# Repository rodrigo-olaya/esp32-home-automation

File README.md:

# esp32-home-automation
Project to make my home smart using several ESP32 MCUs, and sensors.

## Layout
- [temperature-control](temperature-control): temperature and humidity monitoring (the old thermostat motor code is in `temperature-control/legacy/motor`)
- [bringup](bringup): small programs to check the DevKit and the carrier board, flashed with `make flash-<name>`
- [security-camera](security-camera): camera node publishing frames over MQTT
- [hardware/esp32_carrier_board](hardware/esp32_carrier_board): carrier PCB for the DevKit

All nodes talk MQTT to the broker on the Raspberry Pi and are built with ESP-IDF.

## Main Components
This Smart Home system has the following features:
- Temperature Monitoring
- Humidity Monitoring
- Security Camera

### Temperature Monitoring
Temperature is monitored using a DS18B20 sensor, which uses the 1-Wire protocol to communicate with an ESP32.

### Humidity Monitoring
Humidity is monitored using an SHT31 sensor, which uses I2C to communicate with ESP32

## Hardware
The ESP32 home node carrier board (KiCad project, Gerbers, BOM, renders) is in [hardware/esp32_carrier_board](hardware/esp32_carrier_board).

Top and bottom views: [render_top.png](hardware/esp32_carrier_board/fab/render_top.png), [render_bottom.png](hardware/esp32_carrier_board/fab/render_bottom.png).

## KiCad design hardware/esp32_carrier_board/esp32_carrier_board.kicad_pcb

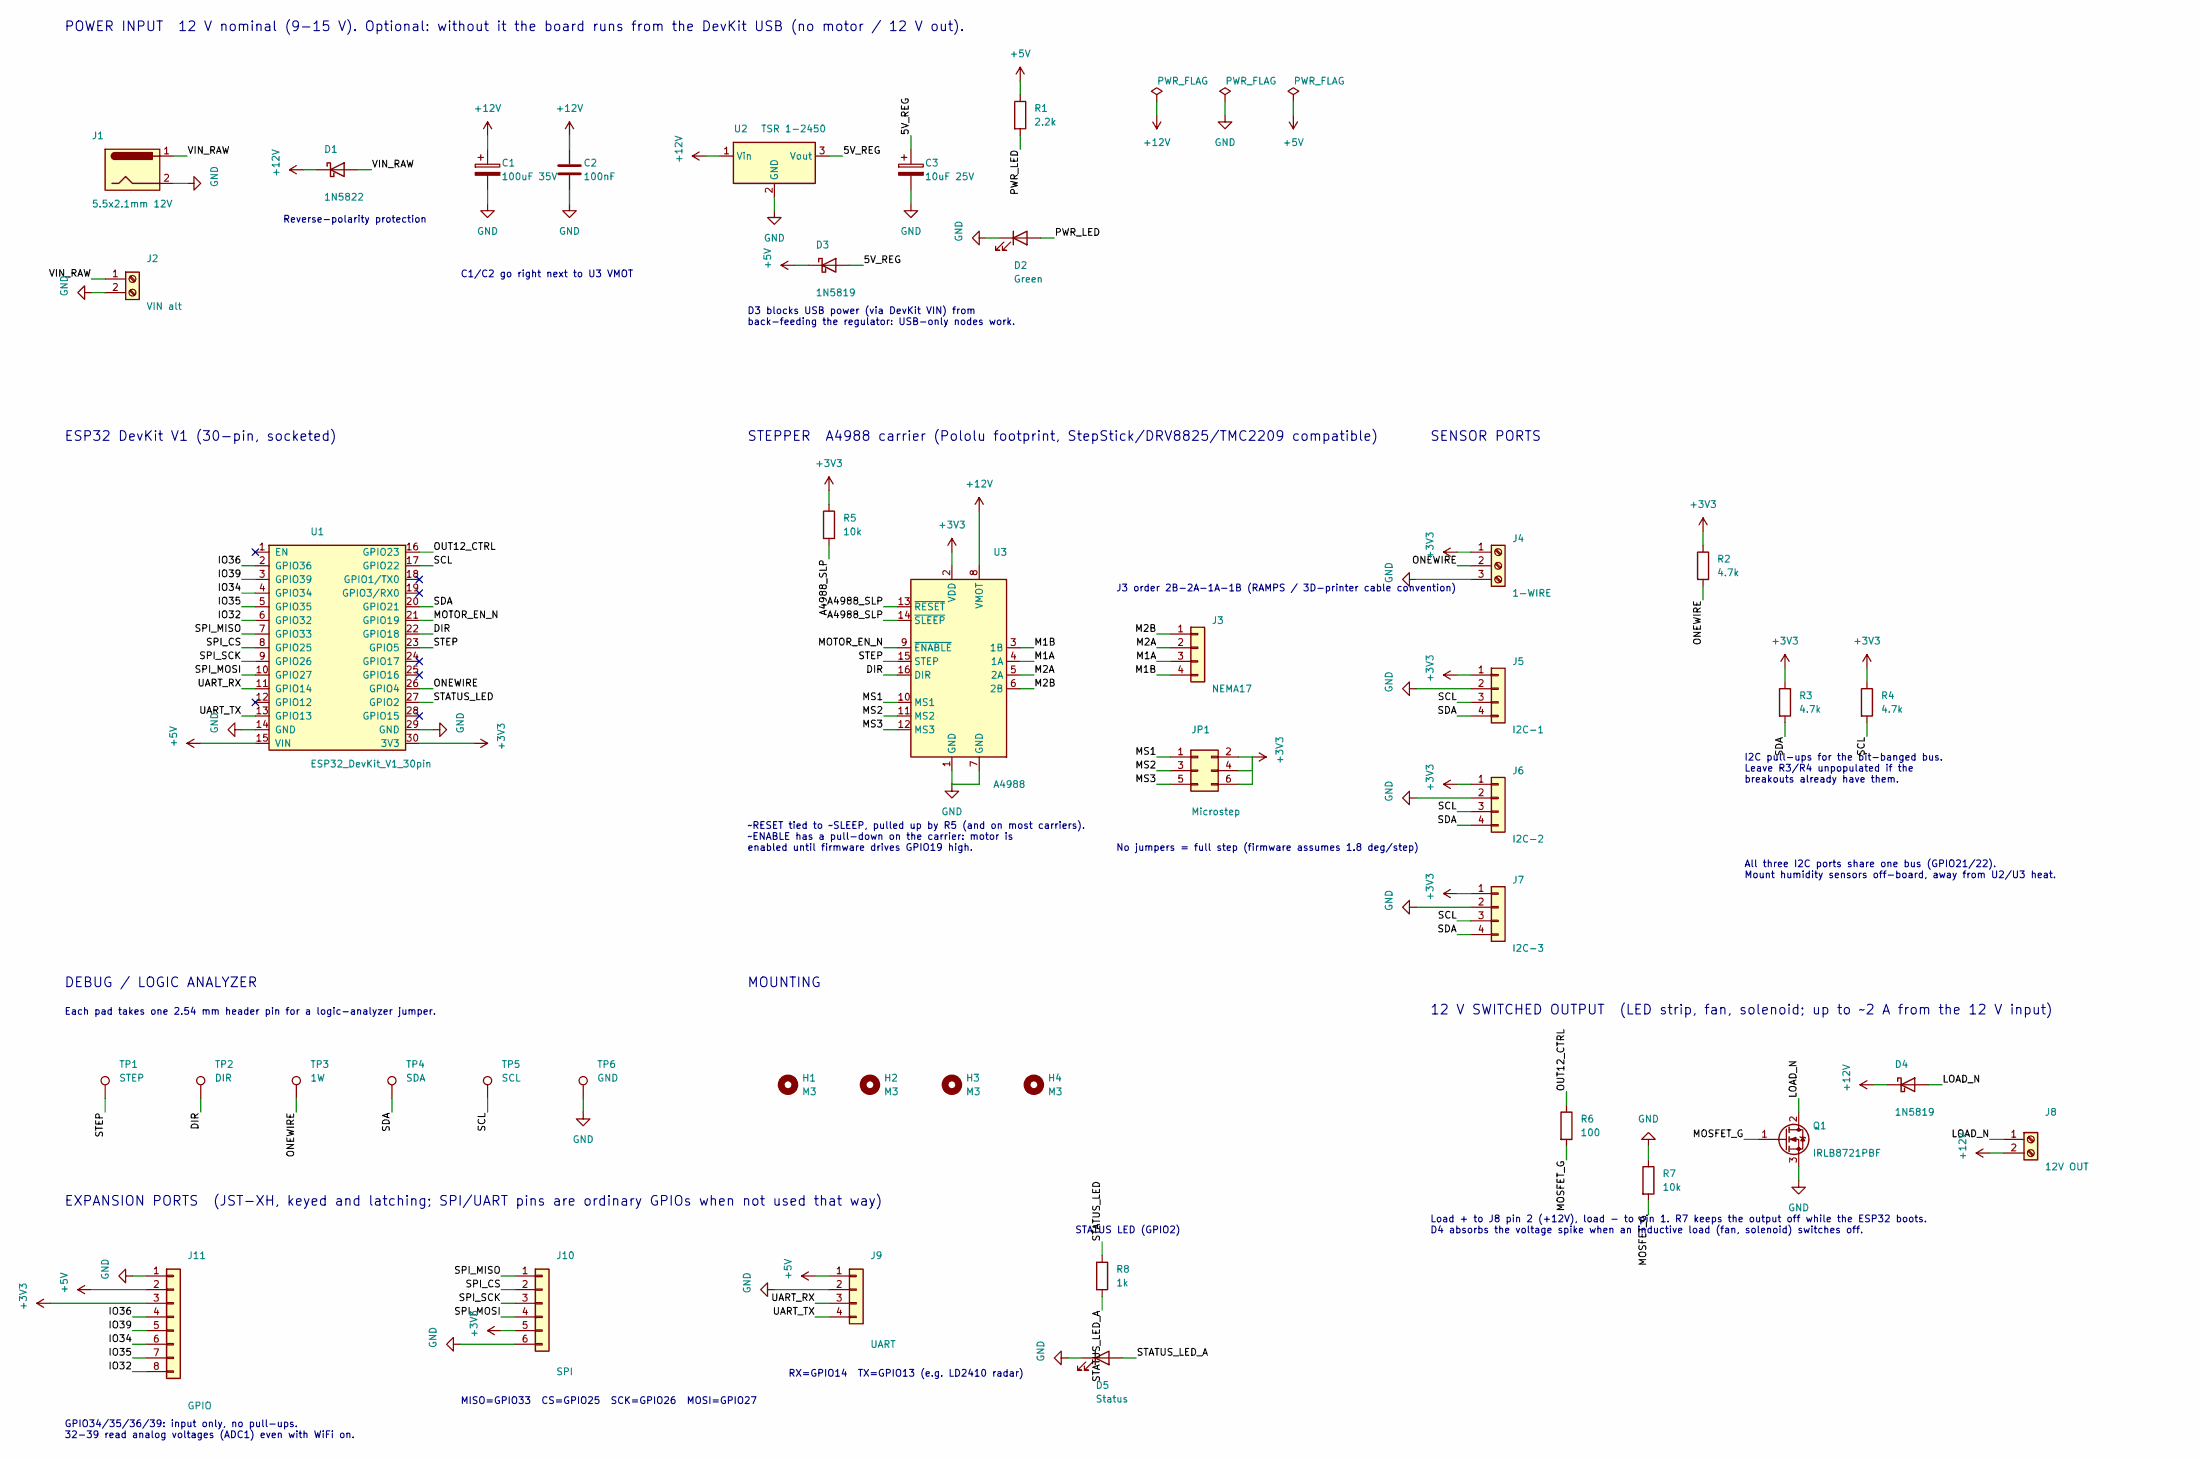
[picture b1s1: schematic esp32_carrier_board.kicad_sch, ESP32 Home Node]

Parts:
C1: 100uF 35V; CP_Radial_D8.0mm_P3.50mm
C2: 100nF; C_Disc_D5.0mm_W2.5mm_P5.00mm
C3: 10uF 25V; CP_Radial_D5.0mm_P2.00mm
D1: 1N5822; D_DO-201AD_P15.24mm_Horizontal
D2: Green; LED_D5.0mm
D3, D4: 1N5819; D_DO-41_SOD81_P2.54mm_Vertical_AnodeUp
D5: Status; LED_D5.0mm
H1, H2, H3, H4: M3; MountingHole_3.2mm_M3
J1: 5.5x2.1mm 12V; BarrelJack_Horizontal
J2: VIN alt; TerminalBlock_Phoenix_MKDS-1,5-2-5.08_1x02_P5.08mm_Horizont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
J3: NEMA17; JST_XH_B4B-XH-A_1x04_P2.50mm_Vertical
J4: 1-WIRE; TerminalBlock_Phoenix_MKDS-1,5-3-5.08_1x03_P5.08mm_Horizont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
J5: I2C-1; JST_XH_B4B-XH-A_1x04_P2.50mm_Vertical
J6: I2C-2; JST_XH_B4B-XH-A_1x04_P2.50mm_Vertical
J7: I2C-3; JST_XH_B4B-XH-A_1x04_P2.50mm_Vertical
J8: 12V OUT; TerminalBlock_Phoenix_MKDS-1,5-2-5.08_1x02_P5.08mm_Horizont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
J9: UART; JST_XH_B4B-XH-A_1x04_P2.50mm_Vertical
J10: SPI; JST_XH_B6B-XH-A_1x06_P2.50mm_Vertical
J11: GPIO; JST_XH_B8B-XH-A_1x08_P2.50mm_Vertical
JP1: Microstep; PinHeader_2x03_P2.54mm_Vertical
Q1: IRLB8721PBF; TO-220-3_Vertical
R1: 2.2k; R_Axial_DIN0207_L6.3mm_D2.5mm_P10.16mm_Horizontal
R2, R3, R4: 4.7k; R_Axial_DIN0207_L6.3mm_D2.5mm_P10.16mm_Horizontal
R5: 10k; R_Axial_DIN0207_L6.3mm_D2.5mm_P10.16mm_Horizontal
R6: 100; R_Axial_DIN0207_L6.3mm_D2.5mm_P2.54mm_Vertical
R7: 10k; R_Axial_DIN0207_L6.3mm_D2.5mm_P2.54mm_Vertical
R8: 1k; R_Axial_DIN0207_L6.3mm_D2.5mm_P7.62mm_Horizontal
TP1: STEP; TestPoint_THTPad_D2.0mm_Drill1.0mm
TP2: DIR; TestPoint_THTPad_D2.0mm_Drill1.0mm
TP3: 1W; TestPoint_THTPad_D2.0mm_Drill1.0mm
TP4: SDA; TestPoint_THTPad_D2.0mm_Drill1.0mm
TP5: SCL; TestPoint_THTPad_D2.0mm_Drill1.0mm
TP6: GND; TestPoint_THTPad_D2.0mm_Drill1.0mm
U1: ESP32_DevKit_V1_30pin; ESP32_DevKit_V1_30pin_Socket
U2: TSR 1-2450; Converter_DCDC_TRACO_TSR-1_THT
U3: A4988; Pololu_Breakout-16_15.2x20.3mm

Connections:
+3V3: J4.1, J5.1, J6.1, J7.1, J10.5, J11.3, JP1.2, JP1.4, JP1.6, R2.1, R3.1, R4.1, R5.1, U1.30 (3V3), U3.2 (VDD)
+5V: D3.1 (K), J9.1, J11.2, R1.1, U1.15 (VIN)
+12V: C1.1, C2.1, D1.1 (K), D4.1 (K), J8.2, U2.1 (Vin), U3.8 (VMOT)
/5V_REG: C3.1, D3.2 (A), U2.3 (Vout)
/A4988_SLP: R5.2, U3.13 (~RESET), U3.14 (~SLEEP)
/DIR: TP2.1, U1.22 (GPIO18), U3.16 (DIR)
/IO32: J11.8, U1.6 (GPIO32)
/IO34: J11.6, U1.4 (GPIO34)
/IO35: J11.7, U1.5 (GPIO35)
/IO36: J11.4, U1.2 (GPIO36)
/IO39: J11.5, U1.3 (GPIO39)
/LOAD_N: D4.2 (A), J8.1, Q1.2 (D)
/M1A: J3.3, U3.4 (1A)
/M1B: J3.4, U3.3 (1B)
/M2A: J3.2, U3.5 (2A)
/M2B: J3.1, U3.6 (2B)
/MOSFET_G: Q1.1 (G), R6.2, R7.2
/MOTOR_EN_N: U1.21 (GPIO19), U3.9 (~ENABLE)
/MS1: JP1.1, U3.10 (MS1)
/MS2: JP1.3, U3.11 (MS2)
/MS3: JP1.5, U3.12 (MS3)
/ONEWIRE: J4.2, R2.2, TP3.1, U1.26 (GPIO4)
/OUT12_CTRL: R6.1, U1.16 (GPIO23)
/PWR_LED: D2.2 (A), R1.2
/SCL: J5.3, J6.3, J7.3, R4.2, TP5.1, U1.17 (GPIO22)
/SDA: J5.4, J6.4, J7.4, R3.2, TP4.1, U1.20 (GPIO21)
/SPI_CS: J10.2, U1.8 (GPIO25)
/SPI_MISO: J10.1, U1.7 (GPIO33)
/SPI_MOSI: J10.4, U1.10 (GPIO27)
/SPI_SCK: J10.3, U1.9 (GPIO26)
/STATUS_LED: R8.1, U1.27 (GPIO2)
/STATUS_LED_A: D5.2 (A), R8.2
/STEP: TP1.1, U1.23 (GPIO5), U3.15 (STEP)
/UART_RX: J9.3, U1.11 (GPIO14)
/UART_TX: J9.4, U1.13 (GPIO13)
/VIN_RAW: D1.2 (A), J1.1, J2.1
GND: C1.2, C2.2, C3.2, D2.1 (K), D5.1 (K), J1.2, J2.2, J4.3, J5.2, J6.2, J7.2, J9.2, J10.6, J11.1, Q1.3 (S), R7.1, TP6.1, U1.14 (GND), U1.29 (GND), U2.2 (GND), U3.1 (GND), U3.7 (GND)

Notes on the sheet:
POWER INPUT 12 V nominal (9-15 V). Optional: without it the board runs from the DevKit USB (no motor / 12 V out).
Reverse-polarity protection
C1/C2 go right next to U3 VMOT
D3 blocks USB power (via DevKit VIN) from back-feeding the regulator: USB-only nodes work.
ESP32 DevKit V1 (30-pin, socketed)
STEPPER A4988 carrier (Pololu footprint, StepStick/DRV8825/TMC2209 compatible)
~RESET tied to ~SLEEP, pulled up by R5 (and on most carriers). ~ENABLE has a pull-down on the carrier: motor is enabled until firmware drives GPIO19 high.
No jumpers = full step (firmware assumes 1.8 deg/step)
J3 order 2B-2A-1A-1B (RAMPS / 3D-printer cable convention)
SENSOR PORTS
I2C pull-ups for the bit-banged bus. Leave R3/R4 unpopulated if the breakouts already have them.
All three I2C ports share one bus (GPIO21/22). Mount humidity sensors off-board, away from U2/U3 heat.
DEBUG / LOGIC ANALYZER
Each pad takes one 2.54 mm header pin for a logic-analyzer jumper.
MOUNTING
12 V SWITCHED OUTPUT (LED strip, fan, solenoid; up to ~2 A from the 12 V input)
Load + to J8 pin 2 (+12V), load - to pin 1. R7 keeps the output off while the ESP32 boots. D4 absorbs the voltage spike when an inductive load (fan, solenoid) switches off.
EXPANSION PORTS (JST-XH, keyed and latching; SPI/UART pins are ordinary GPIOs when not used that way)
GPIO34/35/36/39: input only, no pull-ups. 32-39 read analog voltages (ADC1) even with WiFi on.
MISO=GPIO33 CS=GPIO25 SCK=GPIO26 MOSI=GPIO27
RX=GPIO14 TX=GPIO13 (e.g. LD2410 radar)
STATUS LED (GPIO2)

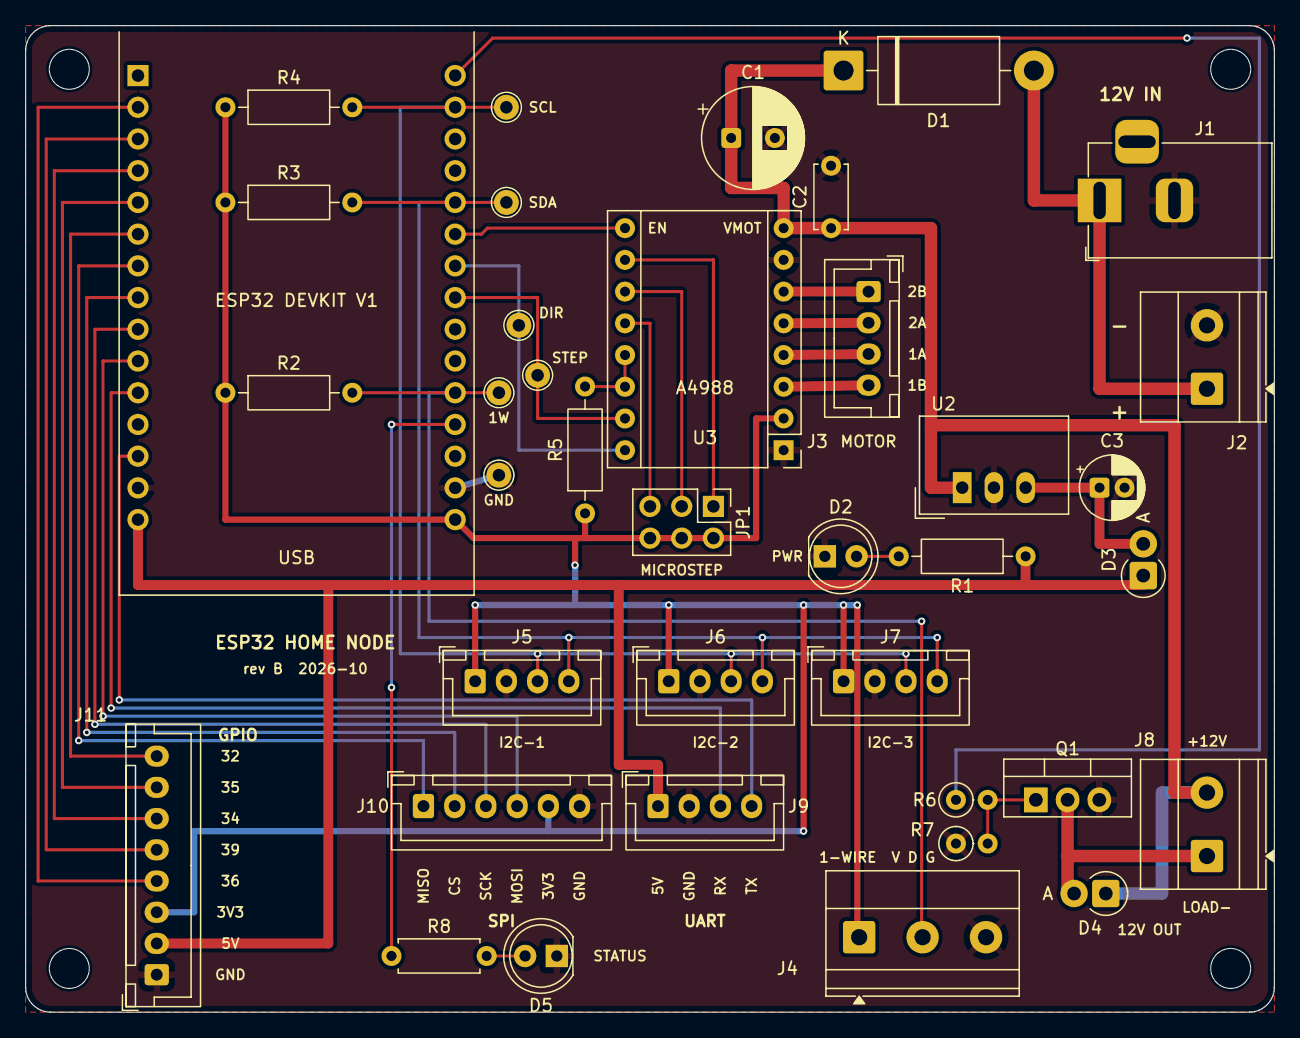
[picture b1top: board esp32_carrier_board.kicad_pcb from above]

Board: 2 copper layers, 100.0 x 79.0 mm, 42 parts (0 on the bottom side), 37 nets.

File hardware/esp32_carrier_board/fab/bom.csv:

"Reference","Value","Footprint","QUANTITY"
"C1","100uF 35V","Capacitor_THT:CP_Radial_D8.0mm_P3.50mm","1"
"C2","100nF","Capacitor_THT:C_Disc_D5.0mm_W2.5mm_P5.00mm","1"
"C3","10uF 25V","Capacitor_THT:CP_Radial_D5.0mm_P2.00mm","1"
"D1","1N5822","Diode_THT:D_DO-201AD_P15.24mm_Horizontal","1"
"D2","Green","LED_THT:LED_D5.0mm","1"
"D3,D4","1N5819","Diode_THT:D_DO-41_SOD81_P2.54mm_Vertical_AnodeUp","2"
"D5","Status","LED_THT:LED_D5.0mm","1"
"J1","5.5x2.1mm 12V","Connector_BarrelJack:BarrelJack_Horizontal","1"
"J2","VIN alt","TerminalBlock_Phoenix:TerminalBlock_Phoenix_MKDS-1,5-2-5.08_1x02_P5.08mm_Horizontal","1"
"J3","NEMA17","Connector_JST:JST_XH_B4B-XH-A_1x04_P2.50mm_Vertical","1"
"J4","1-WIRE","TerminalBlock_Phoenix:TerminalBlock_Phoenix_MKDS-1,5-3-5.08_1x03_P5.08mm_Horizontal","1"
"J5","I2C-1","Connector_JST:JST_XH_B4B-XH-A_1x04_P2.50mm_Vertical","1"
"J6","I2C-2","Connector_JST:JST_XH_B4B-XH-A_1x04_P2.50mm_Vertical","1"
"J7","I2C-3","Connector_JST:JST_XH_B4B-XH-A_1x04_P2.50mm_Vertical","1"
"J8","12V OUT","TerminalBlock_Phoenix:TerminalBlock_Phoenix_MKDS-1,5-2-5.08_1x02_P5.08mm_Horizontal","1"
"J9","UART","Connector_JST:JST_XH_B4B-XH-A_1x04_P2.50mm_Vertical","1"
"J10","SPI","Connector_JST:JST_XH_B6B-XH-A_1x06_P2.50mm_Vertical","1"
"J11","GPIO","Connector_JST:JST_XH_B8B-XH-A_1x08_P2.50mm_Vertical","1"
"JP1","Microstep","Connector_PinHeader_2.54mm:PinHeader_2x03_P2.54mm_Vertical","1"
"Q1","IRLB8721PBF","Package_TO_SOT_THT:TO-220-3_Vertical","1"
"R1","2.2k","Resistor_THT:R_Axial_DIN0207_L6.3mm_D2.5mm_P10.16mm_Horizontal","1"
"R2-R4","4.7k","Resistor_THT:R_Axial_DIN0207_L6.3mm_D2.5mm_P10.16mm_Horizontal","3"
"R5","10k","Resistor_THT:R_Axial_DIN0207_L6.3mm_D2.5mm_P10.16mm_Horizontal","1"
"R6","100","Resistor_THT:R_Axial_DIN0207_L6.3mm_D2.5mm_P2.54mm_Vertical","1"
"R7","10k","Resistor_THT:R_Axial_DIN0207_L6.3mm_D2.5mm_P2.54mm_Vertical","1"
"R8","1k","Resistor_THT:R_Axial_DIN0207_L6.3mm_D2.5mm_P7.62mm_Horizontal","1"
"U1","ESP32_DevKit_V1_30pin","esp_board_fp:ESP32_DevKit_V1_30pin_Socket","1"
"U2","TSR 1-2450","Converter_DCDC:Converter_DCDC_TRACO_TSR-1_THT","1"
"U3","A4988","Module:Pololu_Breakout-16_15.2x20.3mm","1"
